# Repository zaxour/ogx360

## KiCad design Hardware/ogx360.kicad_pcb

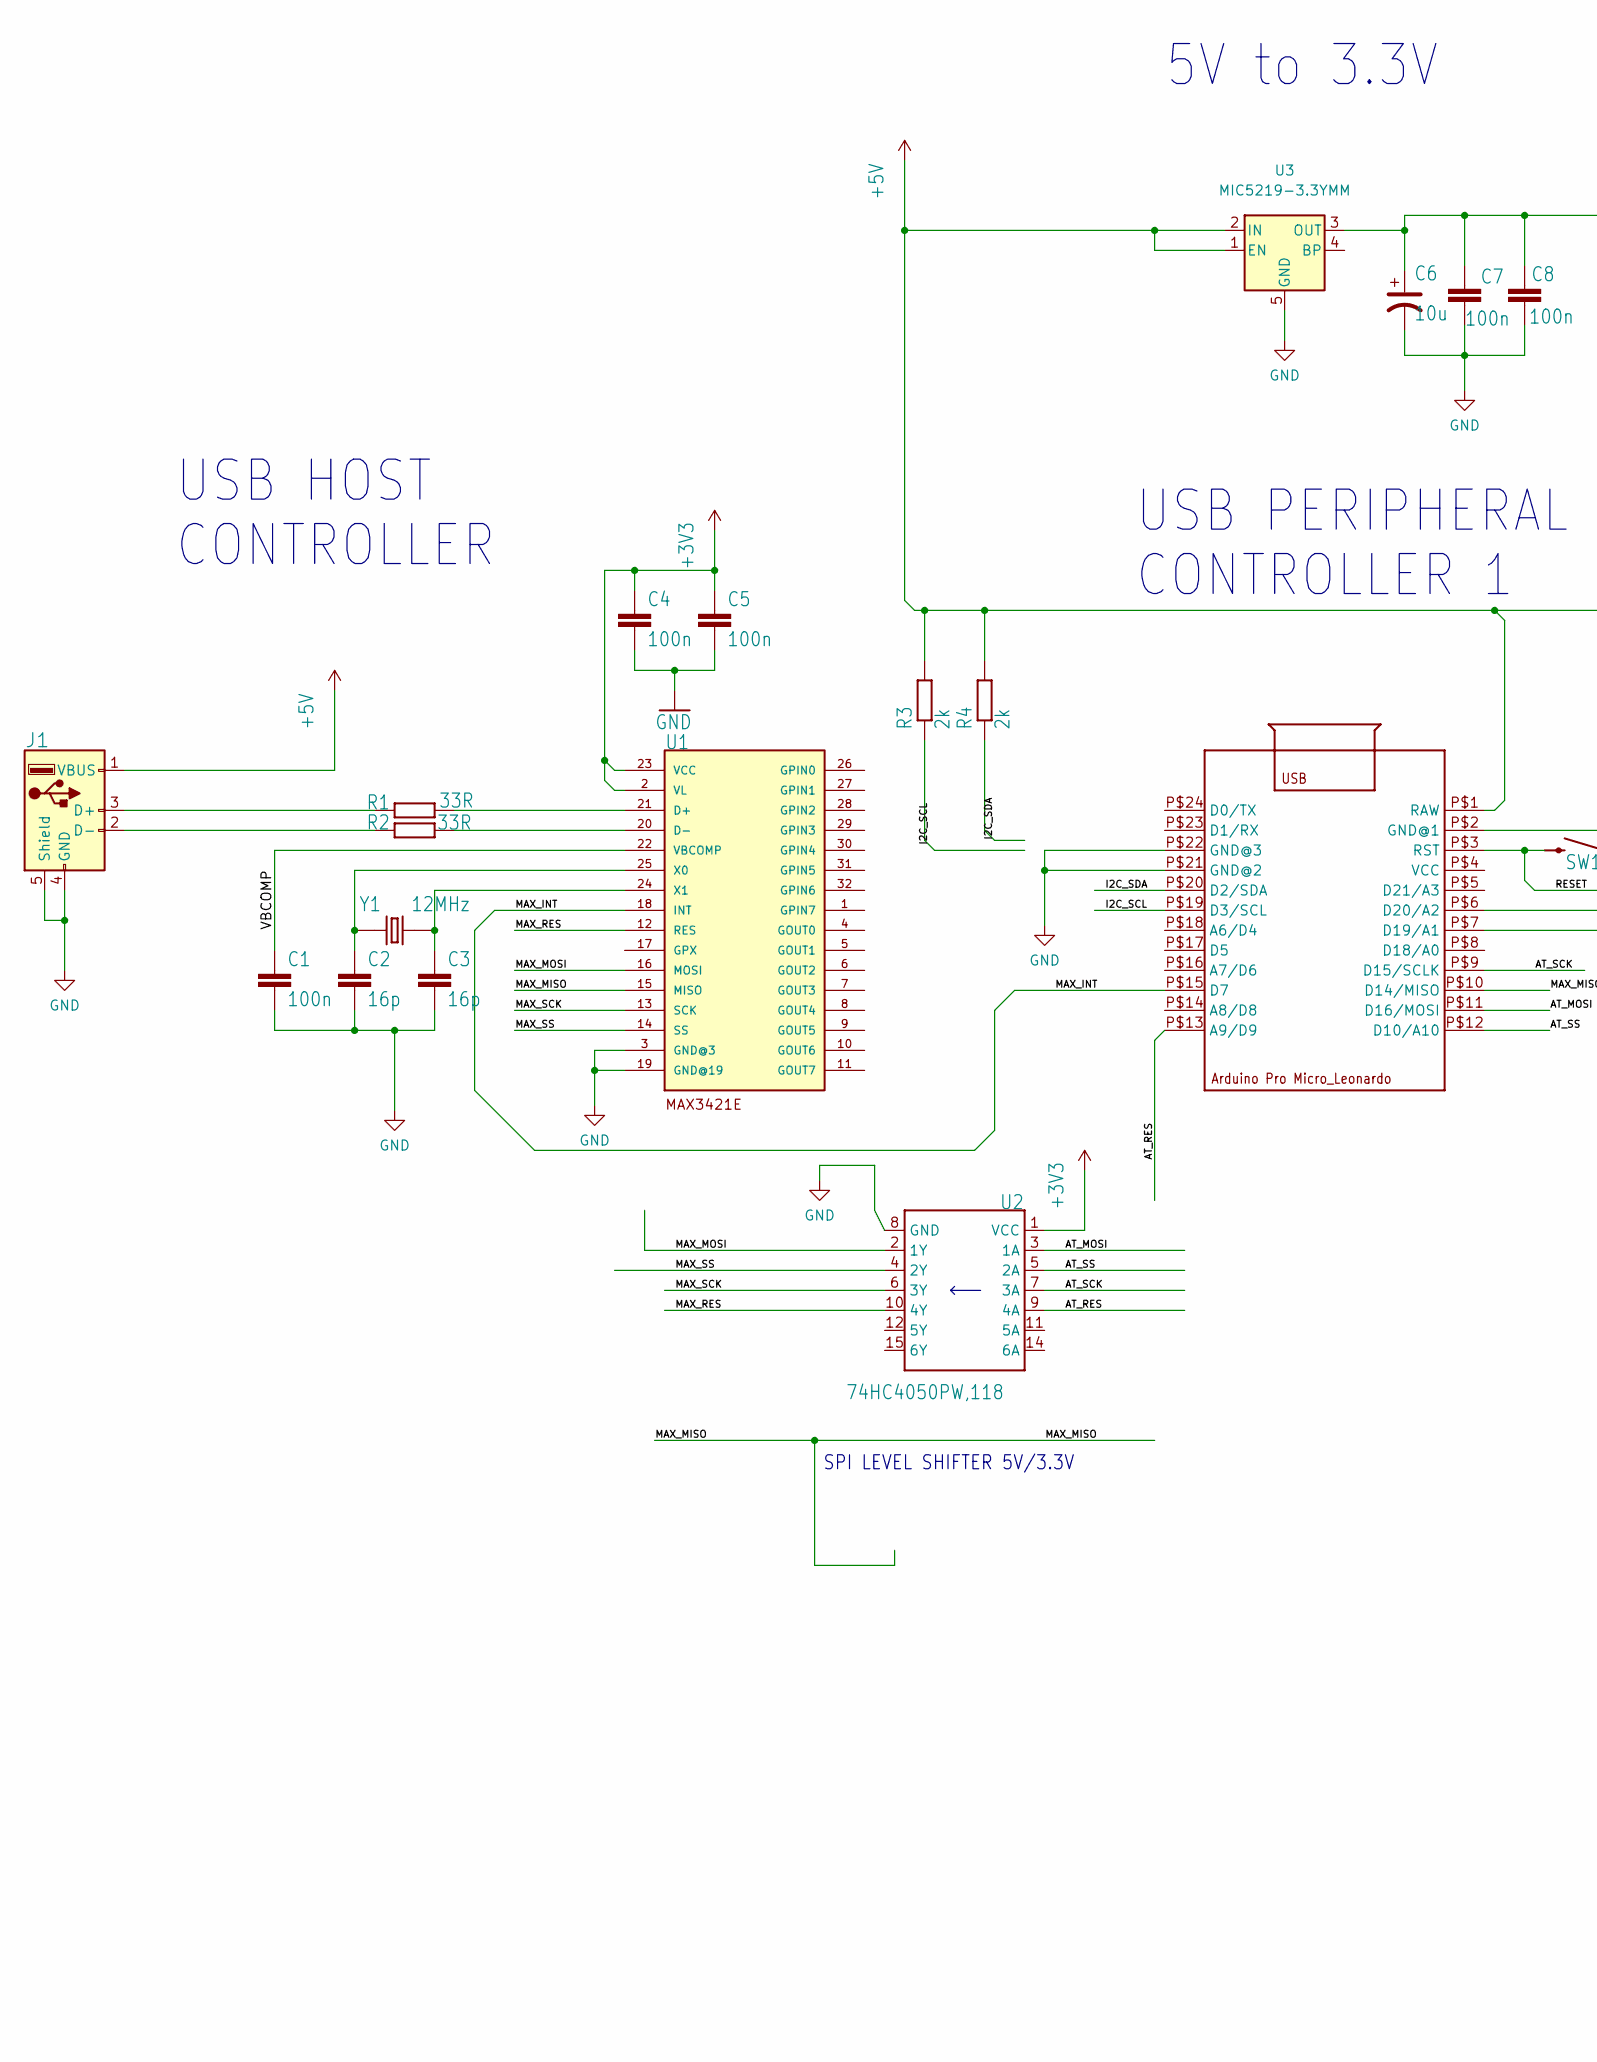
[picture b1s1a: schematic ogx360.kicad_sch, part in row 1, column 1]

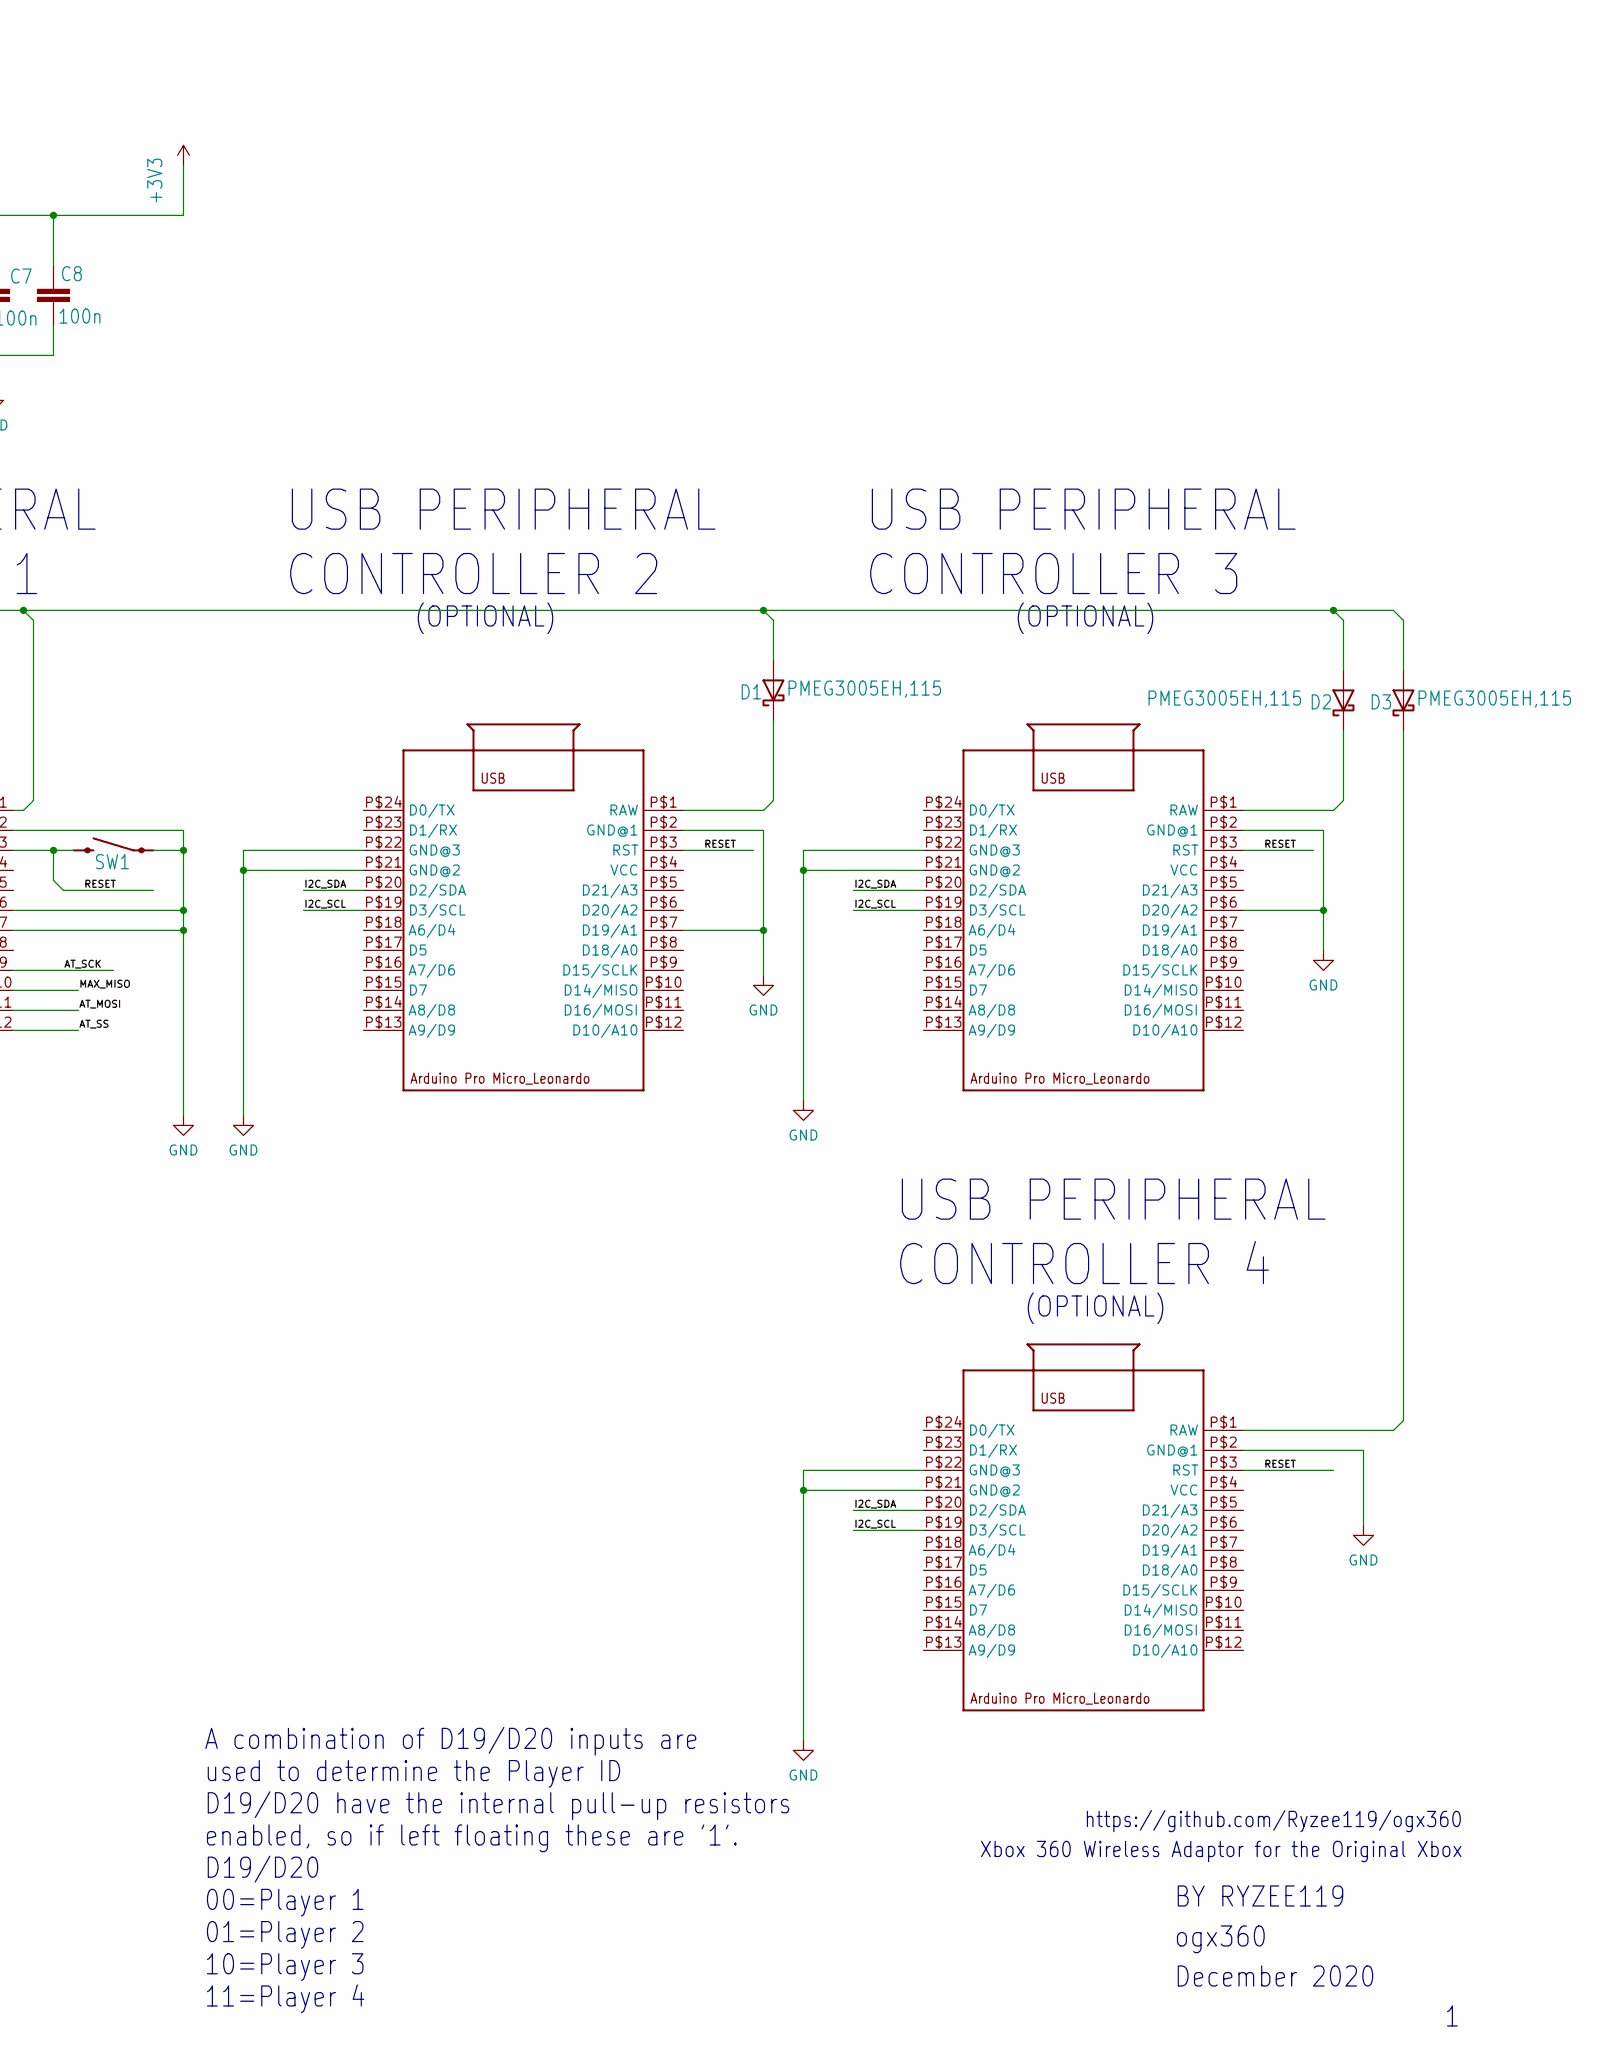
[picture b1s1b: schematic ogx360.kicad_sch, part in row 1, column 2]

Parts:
C1, C4, C5, C7, C8: 100n; C_0805_2012Metric
C2, C3: 16p; C_0805_2012Metric
C6: 10u; CP_Elec_4x5.3
D1, D2, D3: PMEG3005EH,115; D_SOD-123
J1: USB_A_SMT_FEMALE_NS; USB_A_TE_292303-7_Horizontal
R1, R2: 33R; R_0805_2012Metric
R3, R4: 2k; R_0805_2012Metric
SW1: TL3305AF160QG
U1: MAX3421ETQFP32-5MM; TQFP32-5MM
U2: 74HC4050PW,118; TSSOP-16_4.4x5mm_P0.65mm
U3: MIC5219-3.3YMM; MSOP-8_3x3mm_P0.65mm
U4, U5, U6, U7: ARDUINO_LEONARDO_MICRO
Y1: 12MHz; XTAL_ECS-250-18-5PX-JEM-TR

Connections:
+3V3: C4.1, C5.1, C6.1, C7.1, C8.1, U1.2 (VL), U1.23 (VCC), U2.1 (VCC), U3.3 (OUT)
+5V: D1.2 (A), D2.2 (A), D3.2 (A), J1.1 (VBUS), R3.2, R4.2, U3.1 (EN), U3.2 (IN), U4.P$1 (RAW)
/AT_MOSI: U2.3 (1A), U4.P$11 (D16/MOSI)
/AT_RES: U2.9 (4A), U4.P$13 (A9/D9)
/AT_SCK: U2.7 (3A), U4.P$9 (D15/SCLK)
/AT_SS: U2.5 (2A), U4.P$12 (D10/A10)
/I2C_SCL: R3.1, U4.P$19 (D3/SCL), U5.P$19 (D3/SCL), U6.P$19 (D3/SCL), U7.P$19 (D3/SCL)
/I2C_SDA: R4.1, U4.P$20 (D2/SDA), U5.P$20 (D2/SDA), U6.P$20 (D2/SDA), U7.P$20 (D2/SDA)
/MAX_INT: U1.18 (INT), U4.P$15 (D7)
/MAX_MISO: U1.15 (MISO), U4.P$10 (D14/MISO)
/MAX_MOSI: U1.16 (MOSI), U2.2 (1Y)
/MAX_RES: U1.12 (RES), U2.10 (4Y)
/MAX_SCK: U1.13 (SCK), U2.6 (3Y)
/MAX_SS: U1.14 (SS), U2.4 (2Y)
/RESET: SW1.P$1, SW1.P$2, U4.P$3 (RST), U5.P$3 (RST), U6.P$3 (RST), U7.P$3 (RST)
/VBCOMP: C1.1, U1.22 (VBCOMP)
GND: C1.2, C2.2, C3.2, C4.2, C5.2, C6.2, C7.2, C8.2, J1.4 (GND), J1.5 (Shield), SW1.P$3 (2), SW1.P$4 (2), U1.3 (GND@3), U1.19 (GND@19), U2.8 (GND), U3.5 (GND), U3.6 (GND), U3.7 (GND), U3.8 (GND), U4.P$2 (GND@1), U4.P$6 (D20/A2), U4.P$7 (D19/A1), U4.P$21 (GND@2), U4.P$22 (GND@3), U5.P$2 (GND@1), U5.P$7 (D19/A1), U5.P$21 (GND@2), U5.P$22 (GND@3), U6.P$2 (GND@1), U6.P$6 (D20/A2), U6.P$21 (GND@2), U6.P$22 (GND@3), U7.P$2 (GND@1), U7.P$21 (GND@2), U7.P$22 (GND@3)
unnamed: C2.1, U1.25 (X0), Y1.1
unnamed: C3.1, U1.24 (X1), Y1.2
unnamed: D1.1 (K), U5.P$1 (RAW)
unnamed: D2.1 (K), U6.P$1 (RAW)
unnamed: D3.1 (K), U7.P$1 (RAW)
unnamed: J1.2 (D-), R2.2
unnamed: J1.3 (D+), R1.2
unnamed: R1.1, U1.21 (D+)
unnamed: R2.1, U1.20 (D-)

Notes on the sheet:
A combination of D19/D20 inputs are used to determine the Player ID D19/D20 have the internal pull-up resistors enabled, so if left floating these are '1'. D19/D20 00=Player 1 01=Player 2 10=Player 3 11=Player 4
(OPTIONAL)
USB PERIPHERAL CONTROLLER 2
USB HOST CONTROLLER
USB PERIPHERAL CONTROLLER 1
December 2020
ogx360
https://github.com/Ryzee119/ogx360
USB PERIPHERAL CONTROLLER 3
USB PERIPHERAL CONTROLLER 4
SPI LEVEL SHIFTER 5V/3.3V
BY RYZEE119
5V to 3.3V
Xbox 360 Wireless Adaptor for the Original Xbox

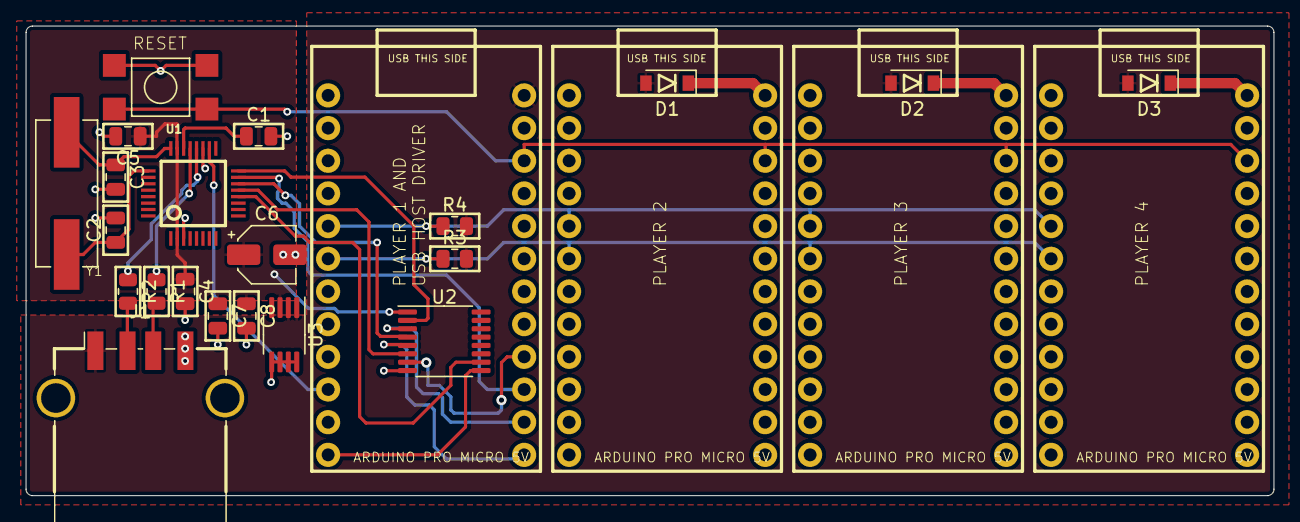
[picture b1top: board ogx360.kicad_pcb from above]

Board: 2 copper layers, 97.0 x 36.5 mm, 25 parts (0 on the bottom side), 26 nets.

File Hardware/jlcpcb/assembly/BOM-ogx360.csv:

Comment,Designator,Footprint,LCSC
"PMEG3005EH,115",D3,D_SOD-123,C179429
"PMEG3005EH,115",D2,D_SOD-123,C179429
"PMEG3005EH,115",D1,D_SOD-123,C179429
MAX3421ETQFP32-5MM,U1,TQFP32-5MM,C45862
USB_A_SMT_FEMALE_NS,J1,USB_A_TE_292303-7_Horizontal,
10u,C6,CP_Elec_4x5.3,
2k,R3,R_0805_2012Metric,C17604
ARDUINO_LEONARDO_MICRO,U7,ARDUINO_LEONARDO_MICRO,
16p,C2,C_0805_2012Metric,C152845
100n,C5,C_0805_2012Metric,C49678
2k,R4,R_0805_2012Metric,C17604
MIC5219-3.3YMM,U3,MSOP-8_3x3mm_P0.65mm,C628154
16p,C3,C_0805_2012Metric,C152845
100n,C8,C_0805_2012Metric,C49678
100n,C7,C_0805_2012Metric,C49678
100n,C4,C_0805_2012Metric,C49678
TL3305AF160QG,SW1,TL3305AF160QG,
ARDUINO_LEONARDO_MICRO,U5,ARDUINO_LEONARDO_MICRO,
33R,R1,R_0805_2012Metric,C17634
ARDUINO_LEONARDO_MICRO,U6,ARDUINO_LEONARDO_MICRO,
12MHz,Y1,XTAL_ECS-250-18-5PX-JEM-TR,
"74HC4050PW,118",U2,TSSOP-16_4.4x5mm_P0.65mm,C546991
ARDUINO_LEONARDO_MICRO,U4,ARDUINO_LEONARDO_MICRO,
100n,C1,C_0805_2012Metric,
33R,R2,R_0805_2012Metric,C17634

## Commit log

2022-08-19 Add files via upload
    Converted Eagle project to KiCAD with appropriate fixes after the import process.
    MIC5219-3.3 regulator footprint changed to MSOP package and 74HC4050 to TSSOP-16 package due to availability. Many symbols migrated over to KiCad library symbols and 3D models assigned.
